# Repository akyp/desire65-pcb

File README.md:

# desire65-pcb
 
 Open-source 65% hotswap pcb. Could be useful for keyboard designers looking for a PCB for gasket or top-mounted boards.
  
 ## Features
 
 - [UDB (Unified DB)](https://unified-daughterboard.github.io) compatibility (JST-SH variant)
 - Hotswap
 - Underglow RGB LEDs
 - Header for in-switch Caps Lock LED (alternative firmware to use it as backlight to be provided)
 - RP2040 MCU
 - QMK/VIA/Vial firmware
 - Holes under 2u stabilizers to facilitate proper keycap installation on long-pole switches
 - Rounded tracks
 - [STEP file](./step/desire65-rounded.step) provided with all the components visible
 - Requires KiCad 8 to modify or produce production files
 - Font used: [Orbitron](https://fonts.google.com/specimen/Orbitron)
 
## Firmware
 - [QMK](https://config.qmk.fm/#/archerkeyboard/desire65/LAYOUT_65_ansi_blocker_tsangan_split_bs)
 - [VIA](https://www.caniusevia.com/docs/download_firmware)
 - [VIAL (with the Caps Lock footprint configured as QMK Backlighting instead)](https://github.com/akyp/desire65-pcb/releases/tag/v1.0_vial_bl)

## Supported Layout

## Renders

## Prototype Photos
1.2mm PCB produced by JLCPCB

## About the holes under 2u stabilizers
It is not easy to fully install a 2/2.25/2.75u keycap on the stabilizer stems when using a long-pole switch with reduced travel. Often one side will be inserted more than the other, causing rattle. The holes on the PCB allow the use of a spare 2u wire underneath to facilitate pushing the stabilizer stems fully into the keycap.

## Plugins Used

 - [marbastlib](https://github.com/ebastler/marbastlib)
 - [Round Tracks](https://github.com/mitxela/kicad-round-tracks)

## If you want to modify the PCB

 - Fork this repo
 - Changes to component placement and tracks must be made to **desire65.kicad_pcb** rather than **desire65-rounded.kicad_pcb**
 - When you're done, use the Round Tracks plugin with **create a new file option** checked to generate a new **desire65-rounded.kicad_pcb**
 - Open it and manually fix track-to-track and track-to-pad clearances. Use DRC to find them.
 - Feel free to ignore the generated **desire65-rounded.kicad_pro**

## Thanks to

 - **Sleepdealr** for the [RP2040 Design Guide](https://github.com/Sleepdealr/RP2040-designguide)
 - **ebastler** for the super-useful [marbastlib](https://github.com/ebastler/marbastlib)
 - **zykrah** for [KiCad KLE Placer](https://github.com/zykrah/kicad-kle-placer) and [Firmware Scripts](https://github.com/zykrah/firmware-scripts)
 - **ai03** for the [PCB Designer Guide](https://wiki.ai03.com/books/pcb-design/chapter/pcb-designer-guide)
 - Folks on Keyboard Atelier Discord

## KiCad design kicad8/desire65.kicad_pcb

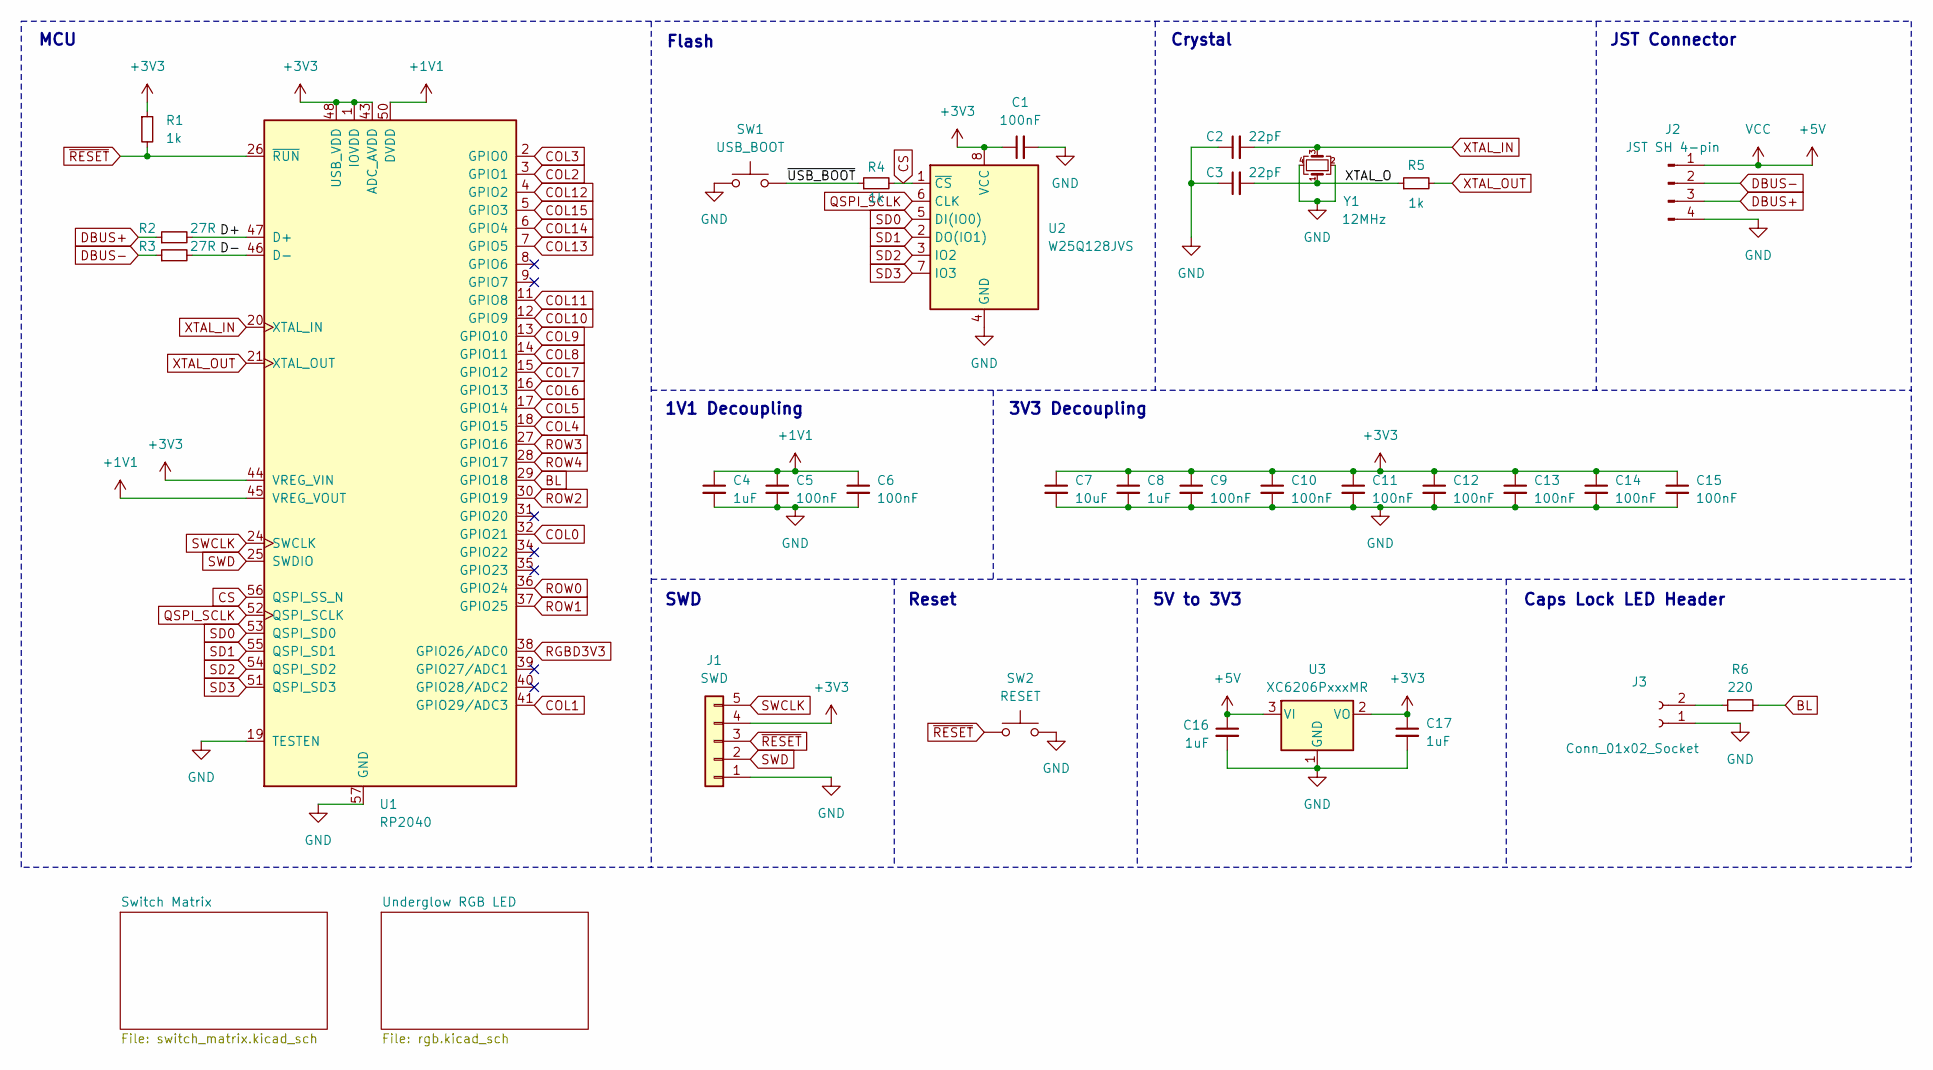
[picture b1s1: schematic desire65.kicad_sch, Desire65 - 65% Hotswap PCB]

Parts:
C1, C5, C6, C9, C10, C11, C12, C13, C14, C15: 100nF; C_0402_1005Metric; LCSC Part C1525
C2, C3: 22pF; C_0402_1005Metric; LCSC Part C1555
C4, C8, C16, C17: 1uF; C_0402_1005Metric; LCSC Part C52923
C7: 10uF; C_0402_1005Metric; LCSC Part C15525
J1: SWD; PinSocket_1x05_P2.54mm_Vertical; JLCPCB BOM 0
J2: JST SH 4-pin; JST_SH_SM04B-SRSS-TB_1x04-1MP_P1.00mm_Horizontal; LCSC Part C371571
J3: Conn_01x02_Socket; LED_MX_3mm; JLCPCB BOM 0
R1, R4, R5: 1k; R_0402_1005Metric; LCSC Part C11702
R2, R3: 27R; R_0603_1608Metric; LCSC Part C25190
R6: 220; R_0402_1005Metric; LCSC Part C25091
SW1: USB_BOOT; SW_SPST_TL3342
SW2: RESET; SW_SPST_TL3342
U1: RP2040; RP2040-QFN-56; LCSC Part C2040
U2: W25Q128JVS; SOIC-8_5.23x5.23mm_P1.27mm; LCSC Part C97521
U3: XC6206PxxxMR; SOT-23; LCSC Part C5446
Y1: 12MHz; Crystal_SMD_3225-4Pin_3.2x2.5mm; LCSC Part C9002

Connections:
+1V1: C4.1, C5.1, C6.1, U1.23 (DVDD), U1.45 (VREG_VOUT), U1.50 (DVDD)
+3V3: C1.1, C7.1, C8.1, C9.1, C10.1, C11.1, C12.1, C13.1, C14.1, C15.1, C17.1, J1.4, R1.1, U1.1 (IOVDD), U1.10 (IOVDD), U1.22 (IOVDD), U1.33 (IOVDD), U1.42 (IOVDD), U1.43 (ADC_AVDD), U1.44 (VREG_VIN), U1.48 (USB_VDD), U1.49 (IOVDD), U2.8 (VCC), U3.2 (VO)
+5V: C16.1, J2.1, U3.3 (VI); also elsewhere on the board
/D+: R2.2, U1.47 (D+)
/D-: R3.2, U1.46 (D-)
/XTAL_O: C3.2, R5.1, Y1.1
/~USB_BOOT: R4.1, SW1.2
BL: R6.2, U1.29 (GPIO18)
COL0: U1.32 (GPIO21); also elsewhere on the board
COL1: U1.41 (GPIO29/ADC3); also elsewhere on the board
COL2: U1.3 (GPIO1); also elsewhere on the board
COL3: U1.2 (GPIO0); also elsewhere on the board
COL4: U1.18 (GPIO15); also elsewhere on the board
COL5: U1.17 (GPIO14); also elsewhere on the board
COL6: U1.16 (GPIO13); also elsewhere on the board
COL7: U1.15 (GPIO12); also elsewhere on the board
COL8: U1.14 (GPIO11); also elsewhere on the board
COL9: U1.13 (GPIO10); also elsewhere on the board
COL10: U1.12 (GPIO9); also elsewhere on the board
COL11: U1.11 (GPIO8); also elsewhere on the board
COL12: U1.4 (GPIO2); also elsewhere on the board
COL13: U1.7 (GPIO5); also elsewhere on the board
COL14: U1.6 (GPIO4); also elsewhere on the board
COL15: U1.5 (GPIO3); also elsewhere on the board
CS: R4.2, U1.56 (QSPI_SS_N), U2.1 (~CS)
DBUS+: J2.3, R2.1
DBUS-: J2.2, R3.1
GND: C1.2, C2.1, C3.1, C4.2, C5.2, C6.2, C7.2, C8.2, C9.2, C10.2, C11.2, C12.2, C13.2, C14.2, C15.2, C16.2, C17.2, J1.1, J2.4, J3.1, SW1.1, SW2.2, U1.19 (TESTEN), U1.57 (GND), U2.4 (GND), U3.1 (GND), Y1.2, Y1.4; also elsewhere on the board
unnamed: J3.2, R6.1
QSPI_SCLK: U1.52 (QSPI_SCLK), U2.6 (CLK)
RGBD3V3: U1.38 (GPIO26/ADC0); also elsewhere on the board
ROW0: U1.36 (GPIO24); also elsewhere on the board
ROW1: U1.37 (GPIO25); also elsewhere on the board
ROW2: U1.30 (GPIO19); also elsewhere on the board
ROW3: U1.27 (GPIO16); also elsewhere on the board
ROW4: U1.28 (GPIO17); also elsewhere on the board
SD0: U1.53 (QSPI_SD0), U2.5 (DI(IO0))
SD1: U1.55 (QSPI_SD1), U2.2 (DO(IO1))
SD2: U1.54 (QSPI_SD2), U2.3 (IO2)
SD3: U1.51 (QSPI_SD3), U2.7 (IO3)
SWCLK: J1.5, U1.24 (SWCLK)
SWD: J1.2, U1.25 (SWDIO)
XTAL_IN: C2.2, U1.20 (XTAL_IN), Y1.3
XTAL_OUT: R5.2, U1.21 (XTAL_OUT)
~RESET: J1.3, R1.2, SW2.1, U1.26 (~RUN)

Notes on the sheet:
JST Connector
5V to 3V3
SWD
MCU
Caps Lock LED Header
1V1 Decoupling
Reset
Flash
Crystal
3V3 Decoupling

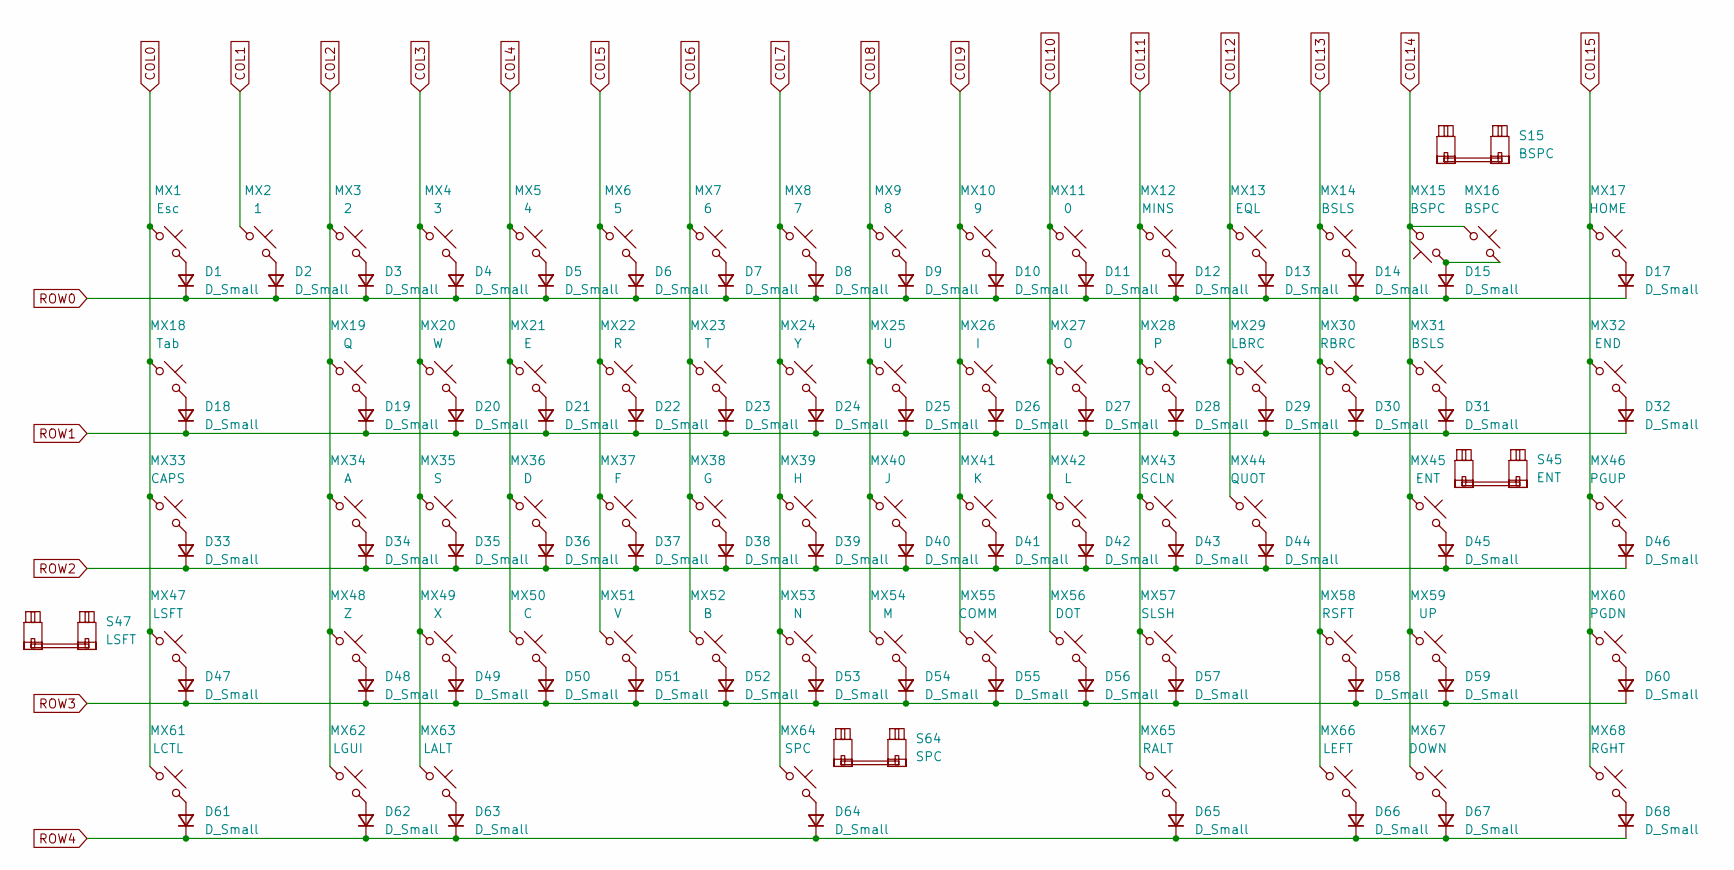
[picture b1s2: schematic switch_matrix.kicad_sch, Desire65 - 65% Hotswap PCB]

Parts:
D1, D2, D3, D4, D5, D6, D7, D8, D9, D10, D11, D12, D13, D14, D15, D17, D18, D19, D20, D21, D22, D23, D24, D25, D26, D27, D28, D29, D30, D31, D32, D33, D34, D35, D36, D37, D38, D39, D40, D41, D42, D43, D44, D45, D46, D47, D48, D49, D50, D51, D52, D53, D54, D55, D56, D57, D58, D59, D60, D61, D62, D63, D64, D65, D66, D67, D68: D_Small; D_SOD-123; LCSC Part C81598
MX1: Esc; SW_MX_HS_CPG151101S11_1u; LCSC Part C5156480
MX2: 1; SW_MX_HS_CPG151101S11_1u; LCSC Part C5156480
MX3: 2; SW_MX_HS_CPG151101S11_1u; LCSC Part C5156480
MX4: 3; SW_MX_HS_CPG151101S11_1u; LCSC Part C5156480
MX5: 4; SW_MX_HS_CPG151101S11_1u; LCSC Part C5156480
MX6: 5; SW_MX_HS_CPG151101S11_1u; LCSC Part C5156480
MX7: 6; SW_MX_HS_CPG151101S11_1u; LCSC Part C5156480
MX8: 7; SW_MX_HS_CPG151101S11_1u; LCSC Part C5156480
MX9: 8; SW_MX_HS_CPG151101S11_1u; LCSC Part C5156480
MX10: 9; SW_MX_HS_CPG151101S11_1u; LCSC Part C5156480
MX11: 0; SW_MX_HS_CPG151101S11_1u; LCSC Part C5156480
MX12: MINS; SW_MX_HS_CPG151101S11_1u; LCSC Part C5156480
MX13: EQL; SW_MX_HS_CPG151101S11_1u; LCSC Part C5156480
MX14: BSLS; SW_MX_HS_CPG151101S11_1u; LCSC Part C5156480
MX15, MX16: BSPC; SW_MX_HS_CPG151101S11_1u; LCSC Part C5156480
MX17: HOME; SW_MX_HS_CPG151101S11_1u; LCSC Part C5156480
MX18: Tab; SW_MX_HS_CPG151101S11_1.5u; LCSC Part C5156480
MX19: Q; SW_MX_HS_CPG151101S11_1u; LCSC Part C5156480
MX20: W; SW_MX_HS_CPG151101S11_1u; LCSC Part C5156480
MX21: E; SW_MX_HS_CPG151101S11_1u; LCSC Part C5156480
MX22: R; SW_MX_HS_CPG151101S11_1u; LCSC Part C5156480
MX23: T; SW_MX_HS_CPG151101S11_1u; LCSC Part C5156480
MX24: Y; SW_MX_HS_CPG151101S11_1u; LCSC Part C5156480
MX25: U; SW_MX_HS_CPG151101S11_1u; LCSC Part C5156480
MX26: I; SW_MX_HS_CPG151101S11_1u; LCSC Part C5156480
MX27: O; SW_MX_HS_CPG151101S11_1u; LCSC Part C5156480
MX28: P; SW_MX_HS_CPG151101S11_1u; LCSC Part C5156480
MX29: LBRC; SW_MX_HS_CPG151101S11_1u; LCSC Part C5156480
MX30: RBRC; SW_MX_HS_CPG151101S11_1u; LCSC Part C5156480
MX31: BSLS; SW_MX_HS_CPG151101S11_1.5u; LCSC Part C5156480
MX32: END; SW_MX_HS_CPG151101S11_1u; LCSC Part C5156480
MX33: CAPS; SW_MX_HS_CPG151101S11_1.75u_STP_1.25; LCSC Part C5156480
MX34: A; SW_MX_HS_CPG151101S11_1u; LCSC Part C5156480
MX35: S; SW_MX_HS_CPG151101S11_1u; LCSC Part C5156480
MX36: D; SW_MX_HS_CPG151101S11_1u; LCSC Part C5156480
MX37: F; SW_MX_HS_CPG151101S11_1u; LCSC Part C5156480
MX38: G; SW_MX_HS_CPG151101S11_1u; LCSC Part C5156480
MX39: H; SW_MX_HS_CPG151101S11_1u; LCSC Part C5156480
MX40: J; SW_MX_HS_CPG151101S11_1u; LCSC Part C5156480
MX41: K; SW_MX_HS_CPG151101S11_1u; LCSC Part C5156480
MX42: L; SW_MX_HS_CPG151101S11_1u; LCSC Part C5156480
MX43: SCLN; SW_MX_HS_CPG151101S11_1u; LCSC Part C5156480
MX44: QUOT; SW_MX_HS_CPG151101S11_1u; LCSC Part C5156480
MX45: ENT; SW_MX_HS_CPG151101S11_1u; LCSC Part C5156480
MX46: PGUP; SW_MX_HS_CPG151101S11_1u; LCSC Part C5156480
MX47: LSFT; SW_MX_HS_CPG151101S11_1u; LCSC Part C5156480
MX48: Z; SW_MX_HS_CPG151101S11_1u; LCSC Part C5156480
MX49: X; SW_MX_HS_CPG151101S11_1u; LCSC Part C5156480
MX50: C; SW_MX_HS_CPG151101S11_1u; LCSC Part C5156480
MX51: V; SW_MX_HS_CPG151101S11_1u; LCSC Part C5156480
MX52: B; SW_MX_HS_CPG151101S11_1u; LCSC Part C5156480
MX53: N; SW_MX_HS_CPG151101S11_1u; LCSC Part C5156480
MX54: M; SW_MX_HS_CPG151101S11_1u; LCSC Part C5156480
MX55: COMM; SW_MX_HS_CPG151101S11_1u; LCSC Part C5156480
MX56: DOT; SW_MX_HS_CPG151101S11_1u; LCSC Part C5156480
MX57: SLSH; SW_MX_HS_CPG151101S11_1u; LCSC Part C5156480
MX58: RSFT; SW_MX_HS_CPG151101S11_1.75u; LCSC Part C5156480
MX59: UP; SW_MX_HS_CPG151101S11_1u; LCSC Part C5156480
MX60: PGDN; SW_MX_HS_CPG151101S11_1u; LCSC Part C5156480
MX61: LCTL; SW_MX_HS_CPG151101S11_1.5u; LCSC Part C5156480
MX62: LGUI; SW_MX_HS_CPG151101S11_1u; LCSC Part C5156480
MX63: LALT; SW_MX_HS_CPG151101S11_1.5u; LCSC Part C5156480
MX64: SPC; SW_MX_HS_CPG151101S11_1u; LCSC Part C5156480
MX65: RALT; SW_MX_HS_CPG151101S11_1.5u; LCSC Part C5156480
MX66: LEFT; SW_MX_HS_CPG151101S11_1u; LCSC Part C5156480
MX67: DOWN; SW_MX_HS_CPG151101S11_1u; LCSC Part C5156480
MX68: RGHT; SW_MX_HS_CPG151101S11_1u; LCSC Part C5156480
S15: BSPC; STAB_MX_2u; JLCPCB BOM 0
S45: ENT; STAB_MX_2.25u; JLCPCB BOM 0
S47: LSFT; STAB_MX_2.25u; JLCPCB BOM 0
S64: SPC; STAB_MX_7u; JLCPCB BOM 0

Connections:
COL0: MX1.1, MX18.1, MX33.1, MX47.1, MX61.1; also elsewhere on the board
COL1: MX2.1; also elsewhere on the board
COL2: MX3.1, MX19.1, MX34.1, MX48.1, MX62.1; also elsewhere on the board
COL3: MX4.1, MX20.1, MX35.1, MX49.1, MX63.1; also elsewhere on the board
COL4: MX5.1, MX21.1, MX36.1, MX50.1; also elsewhere on the board
COL5: MX6.1, MX22.1, MX37.1, MX51.1; also elsewhere on the board
COL6: MX7.1, MX23.1, MX38.1, MX52.1; also elsewhere on the board
COL7: MX8.1, MX24.1, MX39.1, MX53.1, MX64.1; also elsewhere on the board
COL8: MX9.1, MX25.1, MX40.1, MX54.1; also elsewhere on the board
COL9: MX10.1, MX26.1, MX41.1, MX55.1; also elsewhere on the board
COL10: MX11.1, MX27.1, MX42.1, MX56.1; also elsewhere on the board
COL11: MX12.1, MX28.1, MX43.1, MX57.1, MX65.1; also elsewhere on the board
COL12: MX13.1, MX29.1, MX44.1; also elsewhere on the board
COL13: MX14.1, MX30.1, MX58.1, MX66.1; also elsewhere on the board
COL14: MX15.2, MX16.1, MX31.1, MX45.1, MX59.1, MX67.1; also elsewhere on the board
COL15: MX17.1, MX32.1, MX46.1, MX60.1, MX68.1; also elsewhere on the board
unnamed: D1.2 (A), MX1.2
unnamed: D2.2 (A), MX2.2
unnamed: D3.2 (A), MX3.2
unnamed: D4.2 (A), MX4.2
unnamed: D5.2 (A), MX5.2
unnamed: D6.2 (A), MX6.2
unnamed: D7.2 (A), MX7.2
unnamed: D8.2 (A), MX8.2
unnamed: D9.2 (A), MX9.2
unnamed: D10.2 (A), MX10.2
unnamed: D11.2 (A), MX11.2
unnamed: D12.2 (A), MX12.2
unnamed: D13.2 (A), MX13.2
unnamed: D14.2 (A), MX14.2
unnamed: D15.2 (A), MX15.1, MX16.2
unnamed: D17.2 (A), MX17.2
unnamed: D18.2 (A), MX18.2
unnamed: D19.2 (A), MX19.2
unnamed: D20.2 (A), MX20.2
unnamed: D21.2 (A), MX21.2
unnamed: D22.2 (A), MX22.2
unnamed: D23.2 (A), MX23.2
unnamed: D24.2 (A), MX24.2
unnamed: D25.2 (A), MX25.2
unnamed: D26.2 (A), MX26.2
unnamed: D27.2 (A), MX27.2
unnamed: D28.2 (A), MX28.2
unnamed: D29.2 (A), MX29.2
unnamed: D30.2 (A), MX30.2
unnamed: D31.2 (A), MX31.2
unnamed: D32.2 (A), MX32.2
unnamed: D33.2 (A), MX33.2
unnamed: D34.2 (A), MX34.2
unnamed: D35.2 (A), MX35.2
unnamed: D36.2 (A), MX36.2
unnamed: D37.2 (A), MX37.2
unnamed: D38.2 (A), MX38.2
unnamed: D39.2 (A), MX39.2
unnamed: D40.2 (A), MX40.2
unnamed: D41.2 (A), MX41.2
unnamed: D42.2 (A), MX42.2
unnamed: D43.2 (A), MX43.2
unnamed: D44.2 (A), MX44.2
unnamed: D45.2 (A), MX45.2
unnamed: D46.2 (A), MX46.2
unnamed: D47.2 (A), MX47.2
unnamed: D48.2 (A), MX48.2
unnamed: D49.2 (A), MX49.2
unnamed: D50.2 (A), MX50.2
unnamed: D51.2 (A), MX51.2
unnamed: D52.2 (A), MX52.2
unnamed: D53.2 (A), MX53.2
unnamed: D54.2 (A), MX54.2
unnamed: D55.2 (A), MX55.2
unnamed: D56.2 (A), MX56.2
unnamed: D57.2 (A), MX57.2
unnamed: D58.2 (A), MX58.2
unnamed: D59.2 (A), MX59.2
unnamed: D60.2 (A), MX60.2
unnamed: D61.2 (A), MX61.2
unnamed: D62.2 (A), MX62.2
unnamed: D63.2 (A), MX63.2
unnamed: D64.2 (A), MX64.2
unnamed: D65.2 (A), MX65.2
unnamed: D66.2 (A), MX66.2
unnamed: D67.2 (A), MX67.2
unnamed: D68.2 (A), MX68.2
ROW0: D1.1 (K), D2.1 (K), D3.1 (K), D4.1 (K), D5.1 (K), D6.1 (K), D7.1 (K), D8.1 (K), D9.1 (K), D10.1 (K), D11.1 (K), D12.1 (K), D13.1 (K), D14.1 (K), D15.1 (K), D17.1 (K); also elsewhere on the board
ROW1: D18.1 (K), D19.1 (K), D20.1 (K), D21.1 (K), D22.1 (K), D23.1 (K), D24.1 (K), D25.1 (K), D26.1 (K), D27.1 (K), D28.1 (K), D29.1 (K), D30.1 (K), D31.1 (K), D32.1 (K); also elsewhere on the board
ROW2: D33.1 (K), D34.1 (K), D35.1 (K), D36.1 (K), D37.1 (K), D38.1 (K), D39.1 (K), D40.1 (K), D41.1 (K), D42.1 (K), D43.1 (K), D44.1 (K), D45.1 (K), D46.1 (K); also elsewhere on the board
ROW3: D47.1 (K), D48.1 (K), D49.1 (K), D50.1 (K), D51.1 (K), D52.1 (K), D53.1 (K), D54.1 (K), D55.1 (K), D56.1 (K), D57.1 (K), D58.1 (K), D59.1 (K), D60.1 (K); also elsewhere on the board
ROW4: D61.1 (K), D62.1 (K), D63.1 (K), D64.1 (K), D65.1 (K), D66.1 (K), D67.1 (K), D68.1 (K); also elsewhere on the board

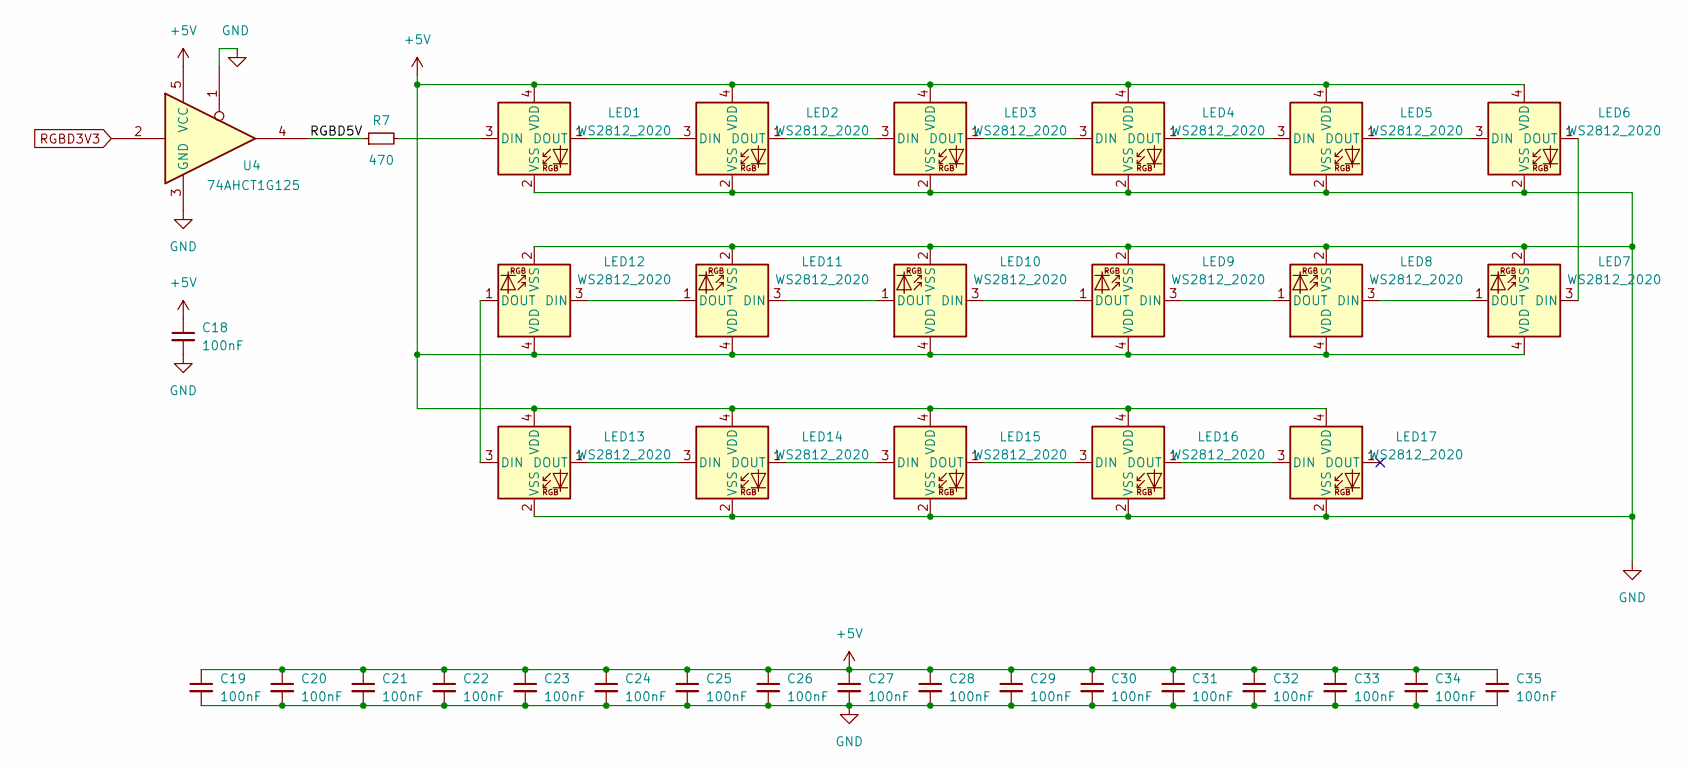
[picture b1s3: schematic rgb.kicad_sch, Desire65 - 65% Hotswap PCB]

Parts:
C18, C19, C20, C21, C22, C23, C24, C25, C26, C27, C28, C29, C30, C31, C32, C33, C34, C35: 100nF; C_0402_1005Metric; LCSC Part C1525
LED1, LED2, LED3, LED4, LED5, LED6, LED7, LED8, LED9, LED10, LED11, LED12, LED13, LED14, LED15, LED16, LED17: WS2812_2020; LED_WS2812_2020; LCSC Part C965555
R7: 470; R_0402_1005Metric; LCSC Part C25117
U4: 74AHCT1G125; SOT-23-5; LCSC Part C7484

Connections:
+5V: C18.1, C19.1, C20.1, C21.1, C22.1, C23.1, C24.1, C25.1, C26.1, C27.1, C28.1, C29.1, C30.1, C31.1, C32.1, C33.1, C34.1, C35.1, LED1.4 (VDD), LED2.4 (VDD), LED3.4 (VDD), LED4.4 (VDD), LED5.4 (VDD), LED6.4 (VDD), LED7.4 (VDD), LED8.4 (VDD), LED9.4 (VDD), LED10.4 (VDD), LED11.4 (VDD), LED12.4 (VDD), LED13.4 (VDD), LED14.4 (VDD), LED15.4 (VDD), LED16.4 (VDD), LED17.4 (VDD), U4.5 (VCC); also elsewhere on the board
/Underglow RGB LED/RGBD5V: R7.1, U4.4
GND: C18.2, C19.2, C20.2, C21.2, C22.2, C23.2, C24.2, C25.2, C26.2, C27.2, C28.2, C29.2, C30.2, C31.2, C32.2, C33.2, C34.2, C35.2, LED1.2 (VSS), LED2.2 (VSS), LED3.2 (VSS), LED4.2 (VSS), LED5.2 (VSS), LED6.2 (VSS), LED7.2 (VSS), LED8.2 (VSS), LED9.2 (VSS), LED10.2 (VSS), LED11.2 (VSS), LED12.2 (VSS), LED13.2 (VSS), LED14.2 (VSS), LED15.2 (VSS), LED16.2 (VSS), LED17.2 (VSS), U4.1, U4.3 (GND); also elsewhere on the board
unnamed: LED1.3 (DIN), R7.2
unnamed: LED1.1 (DOUT), LED2.3 (DIN)
unnamed: LED2.1 (DOUT), LED3.3 (DIN)
unnamed: LED3.1 (DOUT), LED4.3 (DIN)
unnamed: LED4.1 (DOUT), LED5.3 (DIN)
unnamed: LED5.1 (DOUT), LED6.3 (DIN)
unnamed: LED6.1 (DOUT), LED7.3 (DIN)
unnamed: LED7.1 (DOUT), LED8.3 (DIN)
unnamed: LED8.1 (DOUT), LED9.3 (DIN)
unnamed: LED9.1 (DOUT), LED10.3 (DIN)
unnamed: LED10.1 (DOUT), LED11.3 (DIN)
unnamed: LED11.1 (DOUT), LED12.3 (DIN)
unnamed: LED12.1 (DOUT), LED13.3 (DIN)
unnamed: LED13.1 (DOUT), LED14.3 (DIN)
unnamed: LED14.1 (DOUT), LED15.3 (DIN)
unnamed: LED15.1 (DOUT), LED16.3 (DIN)
unnamed: LED16.1 (DOUT), LED17.3 (DIN)
RGBD3V3: U4.2; also elsewhere on the board

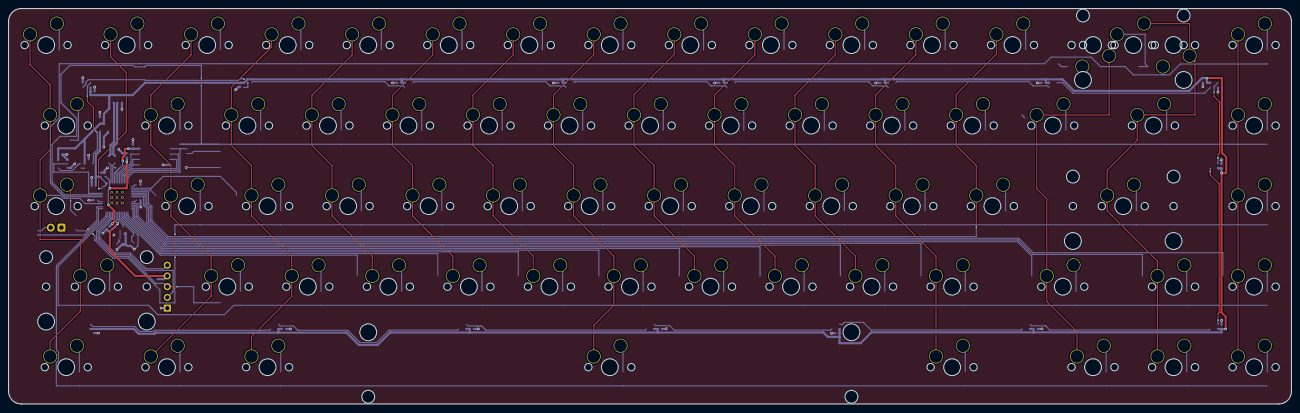
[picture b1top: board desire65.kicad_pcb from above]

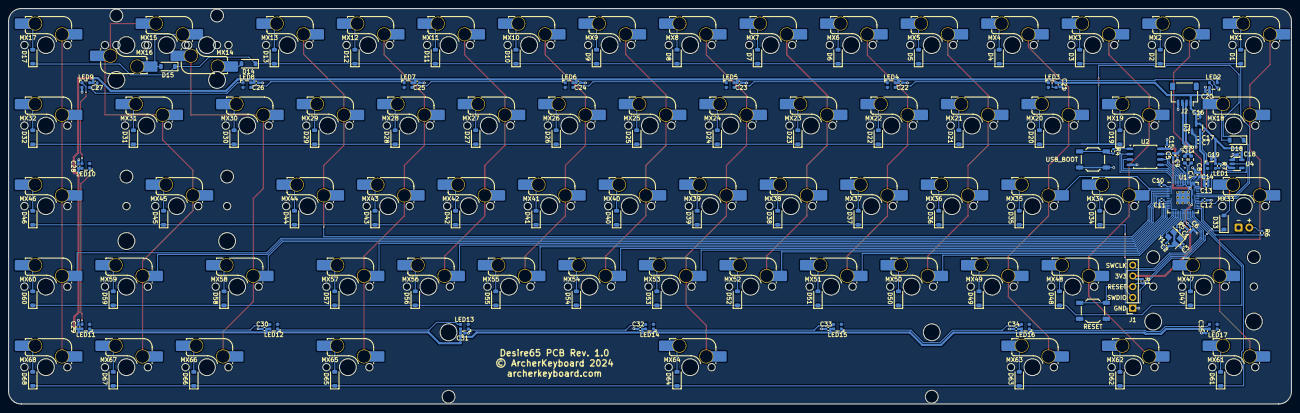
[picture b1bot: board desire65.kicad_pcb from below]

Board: 2 copper layers, 303.5 x 93.5 mm, 208 parts (203 on the bottom side), 130 nets.

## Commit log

2024-05-20 Add font information to readme.md
2024-07-09 Temporary VIAL firmware release
    Temporary VIAL firmware release due to long wait time of merging to QMK
2024-12-18 Update README.md with links to firmware

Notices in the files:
kicad8/desire65.kicad_pcb:
© ArcherKeyboard 2024
